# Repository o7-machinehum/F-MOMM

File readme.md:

# F-MOMM
Flat Micro Outline Memory Module. A RAM memory module for SBC's. See blog post [here](https://machinehum.medium.com/upcycling-laptop-memory-for-single-board-computers-15ed4cf8a675).

## Helping out
This project is in it's infancy. If you're interested in contributing join the [discord here](https://discord.com/invite/EtZT7mjNuM).

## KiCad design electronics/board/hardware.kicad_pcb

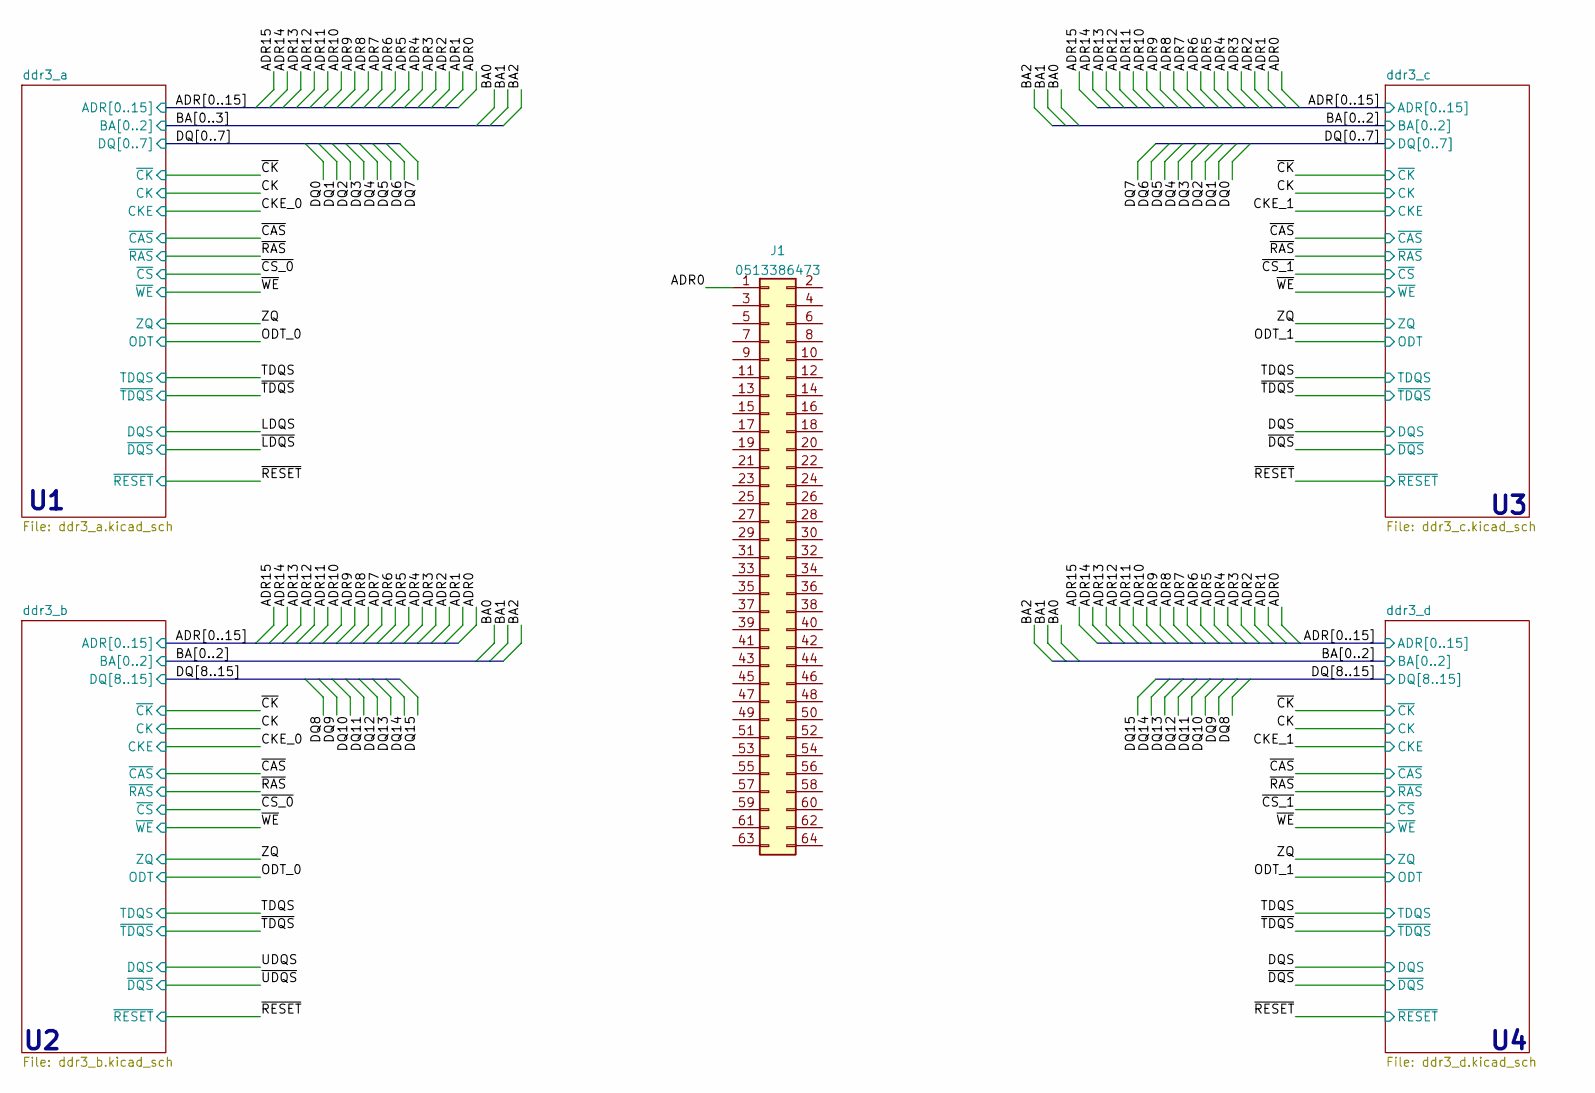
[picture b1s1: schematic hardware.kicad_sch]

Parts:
J1: 0513386473

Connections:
/ADR0: J1.1; also elsewhere on the board

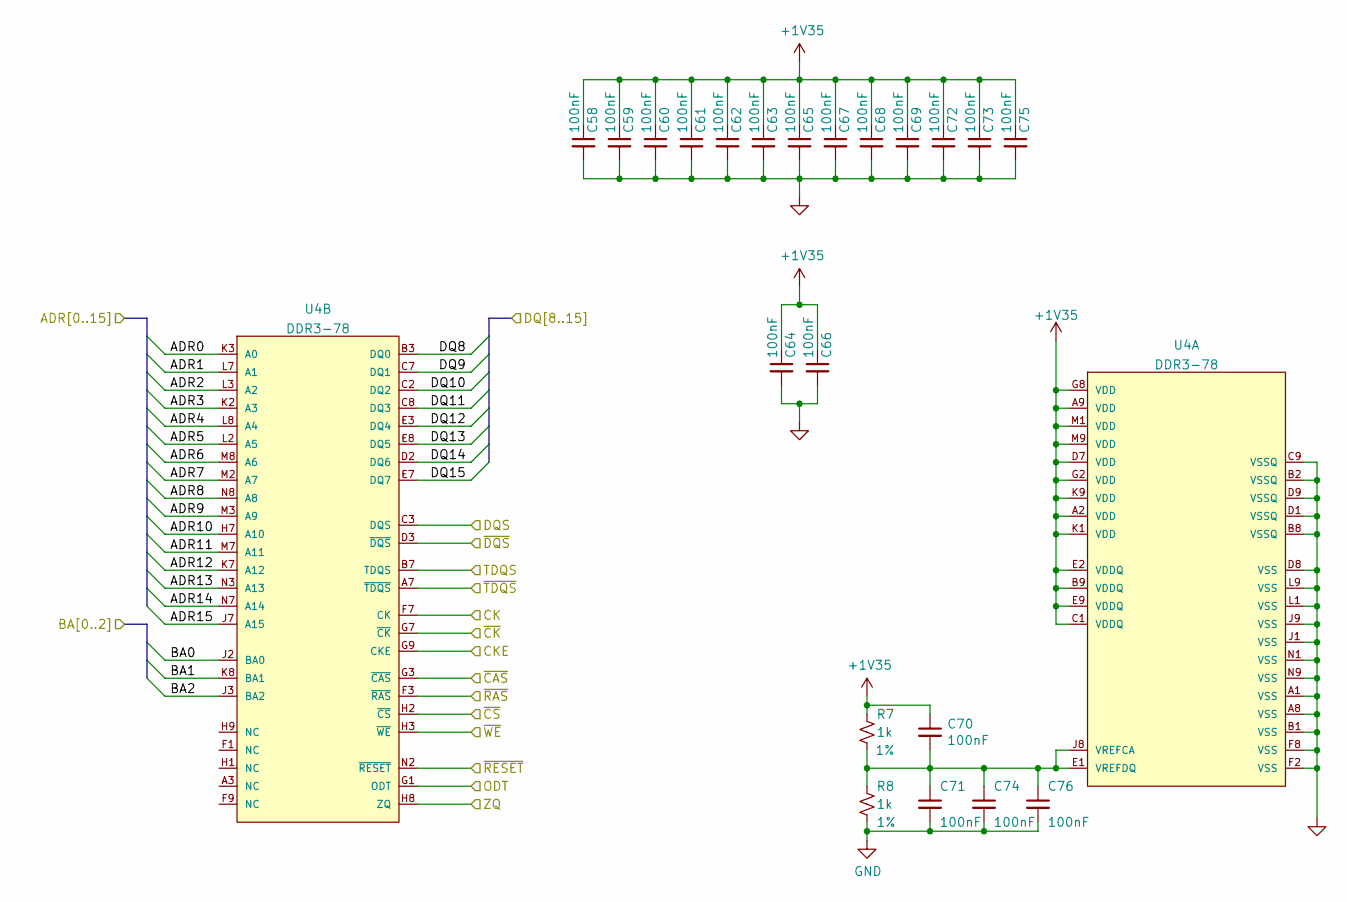
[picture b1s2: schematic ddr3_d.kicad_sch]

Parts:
C58, C59, C60, C61, C62, C63, C64, C65, C66, C67, C68, C69, C70, C71, C72, C73, C74, C75, C76: 100nF; C_0402_1005Metric; MPN CC0402KRX7R7BB104
R7, R8: 1k; R_0402_1005Metric; Tolerance 1%; MPN 4-1879208-9
U4: DDR3-78; DDR3-BGA-78-Tightest

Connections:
+1V35: C58.1, C59.1, C60.1, C61.1, C62.1, C63.1, C64.1, C65.1, C66.1, C67.1, C68.1, C69.1, C70.1, C72.1, C73.1, C75.1, R7.1, U4.A2 (VDD), U4.A9 (VDD), U4.B9 (VDDQ), U4.C1 (VDDQ), U4.D7 (VDD), U4.E2 (VDDQ), U4.E9 (VDDQ), U4.G2 (VDD), U4.G8 (VDD), U4.K1 (VDD), U4.K9 (VDD), U4.M1 (VDD), U4.M9 (VDD); also elsewhere on the board
/ADR0: U4.K3 (A0); also elsewhere on the board
/ADR1: U4.L7 (A1); also elsewhere on the board
/ADR2: U4.L3 (A2); also elsewhere on the board
/ADR3: U4.K2 (A3); also elsewhere on the board
/ADR4: U4.L8 (A4); also elsewhere on the board
/ADR5: U4.L2 (A5); also elsewhere on the board
/ADR6: U4.M8 (A6); also elsewhere on the board
/ADR7: U4.M2 (A7); also elsewhere on the board
/ADR8: U4.N8 (A8); also elsewhere on the board
/ADR9: U4.M3 (A9); also elsewhere on the board
/ADR10: U4.H7 (A10); also elsewhere on the board
/ADR11: U4.M7 (A11); also elsewhere on the board
/ADR12: U4.K7 (A12); also elsewhere on the board
/ADR13: U4.N3 (A13); also elsewhere on the board
/ADR14: U4.N7 (A14); also elsewhere on the board
/ADR15: U4.J7 (A15); also elsewhere on the board
/BA0: U4.J2 (BA0); also elsewhere on the board
/BA1: U4.K8 (BA1); also elsewhere on the board
/BA2: U4.J3 (BA2); also elsewhere on the board
/CK: U4.F7 (CK); also elsewhere on the board
/CKE_1: U4.G9 (CKE); also elsewhere on the board
/DQ8: U4.B3 (DQ0)
/DQ9: U4.C7 (DQ1)
/DQ10: U4.C2 (DQ2)
/DQ11: U4.C8 (DQ3)
/DQ12: U4.E3 (DQ4)
/DQ13: U4.E8 (DQ5)
/DQ14: U4.D2 (DQ6)
/DQ15: U4.E7 (DQ7)
/DQS: U4.C3 (DQS); also elsewhere on the board
/ODT_1: U4.G1 (ODT); also elsewhere on the board
/TDQS: U4.B7 (TDQS); also elsewhere on the board
/ZQ: U4.H8 (ZQ); also elsewhere on the board
/~CAS: U4.G3 (~CAS); also elsewhere on the board
/~CK: U4.G7 (~CK); also elsewhere on the board
/~CS_1: U4.H2 (~CS); also elsewhere on the board
/~DQS: U4.D3 (~DQS); also elsewhere on the board
/~RAS: U4.F3 (~RAS); also elsewhere on the board
/~RESET: U4.N2 (~RESET); also elsewhere on the board
/~TDQS: U4.A7 (~TDQS); also elsewhere on the board
/~WE: U4.H3 (~WE); also elsewhere on the board
GND: C58.2, C59.2, C60.2, C61.2, C62.2, C63.2, C64.2, C65.2, C66.2, C67.2, C68.2, C69.2, C71.2, C72.2, C73.2, C74.2, C75.2, C76.2, R8.2, U4.A1 (VSS), U4.A8 (VSS), U4.B1 (VSS), U4.B2 (VSSQ), U4.B8 (VSSQ), U4.C9 (VSSQ), U4.D1 (VSSQ), U4.D8 (VSS), U4.D9 (VSSQ), U4.F2 (VSS), U4.F8 (VSS), U4.J1 (VSS), U4.J9 (VSS), U4.L1 (VSS), U4.L9 (VSS), U4.N1 (VSS), U4.N9 (VSS); also elsewhere on the board
unnamed: C70.2, C71.1, C74.1, C76.1, R7.2, R8.1, U4.E1 (VREFDQ), U4.J8 (VREFCA)

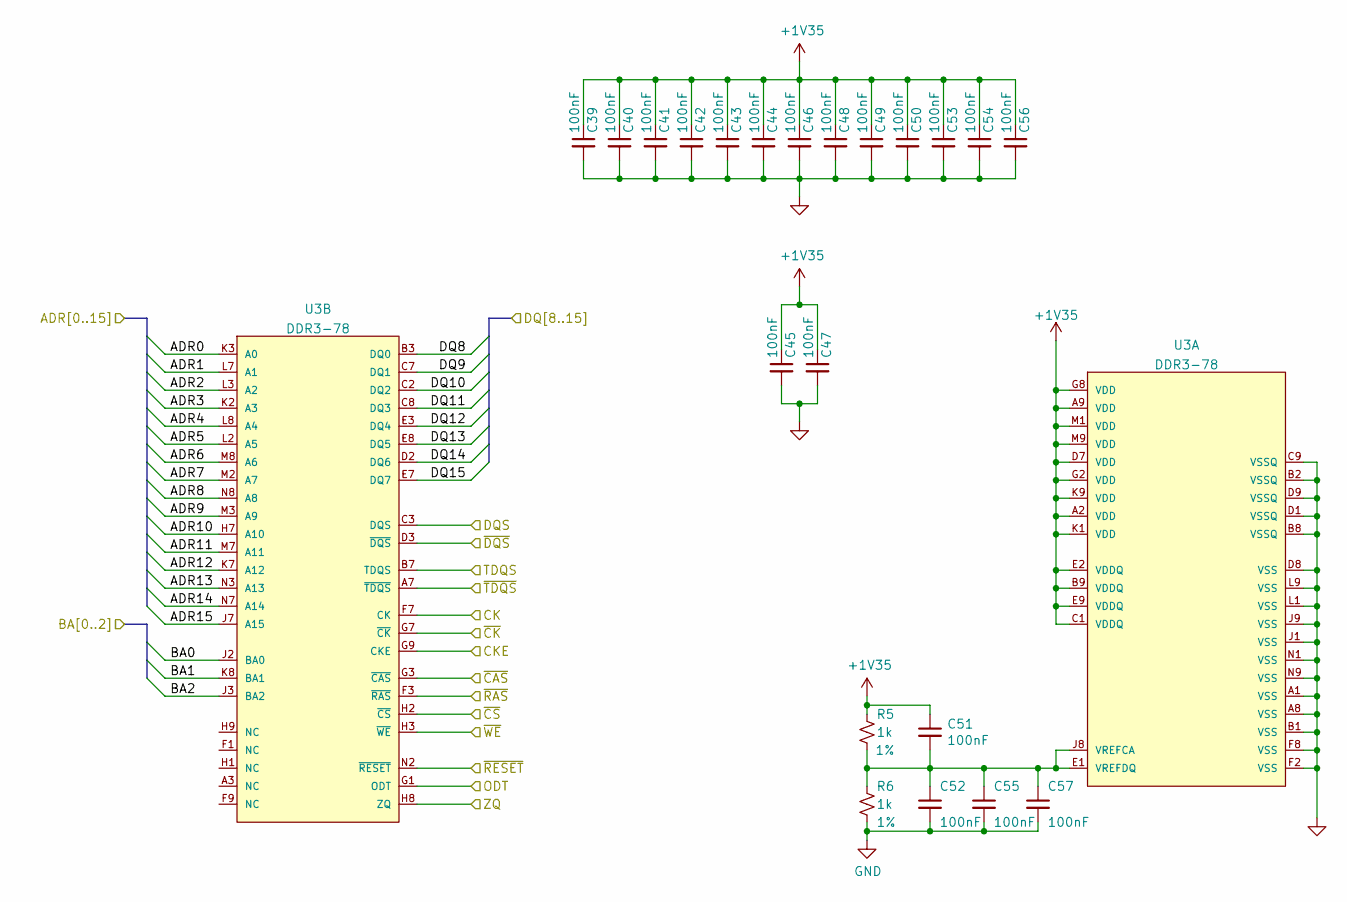
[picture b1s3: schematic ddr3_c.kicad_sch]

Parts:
C39, C40, C41, C42, C43, C44, C45, C46, C47, C48, C49, C50, C51, C52, C53, C54, C55, C56, C57: 100nF; C_0402_1005Metric; MPN CC0402KRX7R7BB104
R5, R6: 1k; R_0402_1005Metric; Tolerance 1%; MPN 4-1879208-9
U3: DDR3-78; DDR3-BGA-78-Tightest

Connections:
+1V35: C39.1, C40.1, C41.1, C42.1, C43.1, C44.1, C45.1, C46.1, C47.1, C48.1, C49.1, C50.1, C51.1, C53.1, C54.1, C56.1, R5.1, U3.A2 (VDD), U3.A9 (VDD), U3.B9 (VDDQ), U3.C1 (VDDQ), U3.D7 (VDD), U3.E2 (VDDQ), U3.E9 (VDDQ), U3.G2 (VDD), U3.G8 (VDD), U3.K1 (VDD), U3.K9 (VDD), U3.M1 (VDD), U3.M9 (VDD); also elsewhere on the board
/ADR0: U3.K3 (A0); also elsewhere on the board
/ADR1: U3.L7 (A1); also elsewhere on the board
/ADR2: U3.L3 (A2); also elsewhere on the board
/ADR3: U3.K2 (A3); also elsewhere on the board
/ADR4: U3.L8 (A4); also elsewhere on the board
/ADR5: U3.L2 (A5); also elsewhere on the board
/ADR6: U3.M8 (A6); also elsewhere on the board
/ADR7: U3.M2 (A7); also elsewhere on the board
/ADR8: U3.N8 (A8); also elsewhere on the board
/ADR9: U3.M3 (A9); also elsewhere on the board
/ADR10: U3.H7 (A10); also elsewhere on the board
/ADR11: U3.M7 (A11); also elsewhere on the board
/ADR12: U3.K7 (A12); also elsewhere on the board
/ADR13: U3.N3 (A13); also elsewhere on the board
/ADR14: U3.N7 (A14); also elsewhere on the board
/ADR15: U3.J7 (A15); also elsewhere on the board
/BA0: U3.J2 (BA0); also elsewhere on the board
/BA1: U3.K8 (BA1); also elsewhere on the board
/BA2: U3.J3 (BA2); also elsewhere on the board
/CK: U3.F7 (CK); also elsewhere on the board
/CKE_1: U3.G9 (CKE); also elsewhere on the board
/DQS: U3.C3 (DQS); also elsewhere on the board
/ODT_1: U3.G1 (ODT); also elsewhere on the board
/TDQS: U3.B7 (TDQS); also elsewhere on the board
/ZQ: U3.H8 (ZQ); also elsewhere on the board
/ddr3_c/DQ8: U3.B3 (DQ0)
/ddr3_c/DQ9: U3.C7 (DQ1)
/ddr3_c/DQ10: U3.C2 (DQ2)
/ddr3_c/DQ11: U3.C8 (DQ3)
/ddr3_c/DQ12: U3.E3 (DQ4)
/ddr3_c/DQ13: U3.E8 (DQ5)
/ddr3_c/DQ14: U3.D2 (DQ6)
/ddr3_c/DQ15: U3.E7 (DQ7)
/~CAS: U3.G3 (~CAS); also elsewhere on the board
/~CK: U3.G7 (~CK); also elsewhere on the board
/~CS_1: U3.H2 (~CS); also elsewhere on the board
/~DQS: U3.D3 (~DQS); also elsewhere on the board
/~RAS: U3.F3 (~RAS); also elsewhere on the board
/~RESET: U3.N2 (~RESET); also elsewhere on the board
/~TDQS: U3.A7 (~TDQS); also elsewhere on the board
/~WE: U3.H3 (~WE); also elsewhere on the board
GND: C39.2, C40.2, C41.2, C42.2, C43.2, C44.2, C45.2, C46.2, C47.2, C48.2, C49.2, C50.2, C52.2, C53.2, C54.2, C55.2, C56.2, C57.2, R6.2, U3.A1 (VSS), U3.A8 (VSS), U3.B1 (VSS), U3.B2 (VSSQ), U3.B8 (VSSQ), U3.C9 (VSSQ), U3.D1 (VSSQ), U3.D8 (VSS), U3.D9 (VSSQ), U3.F2 (VSS), U3.F8 (VSS), U3.J1 (VSS), U3.J9 (VSS), U3.L1 (VSS), U3.L9 (VSS), U3.N1 (VSS), U3.N9 (VSS); also elsewhere on the board
unnamed: C51.2, C52.1, C55.1, C57.1, R5.2, R6.1, U3.E1 (VREFDQ), U3.J8 (VREFCA)

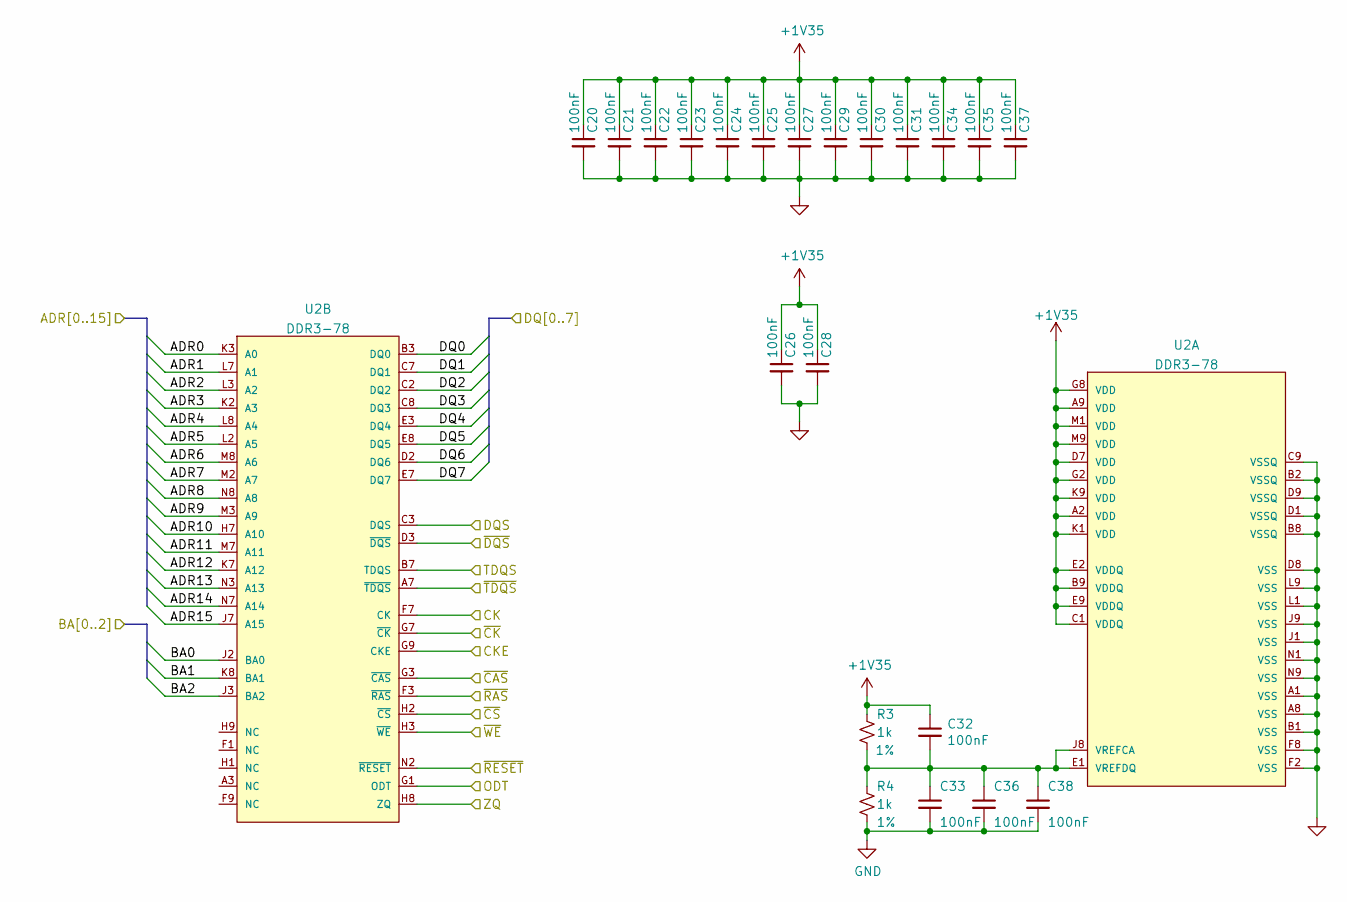
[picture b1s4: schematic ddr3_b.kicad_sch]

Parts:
C20, C21, C22, C23, C24, C25, C26, C27, C28, C29, C30, C31, C32, C33, C34, C35, C36, C37, C38: 100nF; C_0402_1005Metric; MPN CC0402KRX7R7BB104
R3, R4: 1k; R_0402_1005Metric; Tolerance 1%; MPN 4-1879208-9
U2: DDR3-78; DDR3-BGA-78-Tightest

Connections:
+1V35: C20.1, C21.1, C22.1, C23.1, C24.1, C25.1, C26.1, C27.1, C28.1, C29.1, C30.1, C31.1, C32.1, C34.1, C35.1, C37.1, R3.1, U2.A2 (VDD), U2.A9 (VDD), U2.B9 (VDDQ), U2.C1 (VDDQ), U2.D7 (VDD), U2.E2 (VDDQ), U2.E9 (VDDQ), U2.G2 (VDD), U2.G8 (VDD), U2.K1 (VDD), U2.K9 (VDD), U2.M1 (VDD), U2.M9 (VDD); also elsewhere on the board
/ADR0: U2.K3 (A0); also elsewhere on the board
/ADR1: U2.L7 (A1); also elsewhere on the board
/ADR2: U2.L3 (A2); also elsewhere on the board
/ADR3: U2.K2 (A3); also elsewhere on the board
/ADR4: U2.L8 (A4); also elsewhere on the board
/ADR5: U2.L2 (A5); also elsewhere on the board
/ADR6: U2.M8 (A6); also elsewhere on the board
/ADR7: U2.M2 (A7); also elsewhere on the board
/ADR8: U2.N8 (A8); also elsewhere on the board
/ADR9: U2.M3 (A9); also elsewhere on the board
/ADR10: U2.H7 (A10); also elsewhere on the board
/ADR11: U2.M7 (A11); also elsewhere on the board
/ADR12: U2.K7 (A12); also elsewhere on the board
/ADR13: U2.N3 (A13); also elsewhere on the board
/ADR14: U2.N7 (A14); also elsewhere on the board
/ADR15: U2.J7 (A15); also elsewhere on the board
/BA0: U2.J2 (BA0); also elsewhere on the board
/BA1: U2.K8 (BA1); also elsewhere on the board
/BA2: U2.J3 (BA2); also elsewhere on the board
/CK: U2.F7 (CK); also elsewhere on the board
/CKE_0: U2.G9 (CKE); also elsewhere on the board
/ODT_0: U2.G1 (ODT); also elsewhere on the board
/TDQS: U2.B7 (TDQS); also elsewhere on the board
/UDQS: U2.C3 (DQS)
/ZQ: U2.H8 (ZQ); also elsewhere on the board
/ddr3_b/DQ0: U2.B3 (DQ0)
/ddr3_b/DQ1: U2.C7 (DQ1)
/ddr3_b/DQ2: U2.C2 (DQ2)
/ddr3_b/DQ3: U2.C8 (DQ3)
/ddr3_b/DQ4: U2.E3 (DQ4)
/ddr3_b/DQ5: U2.E8 (DQ5)
/ddr3_b/DQ6: U2.D2 (DQ6)
/ddr3_b/DQ7: U2.E7 (DQ7)
/~CAS: U2.G3 (~CAS); also elsewhere on the board
/~CK: U2.G7 (~CK); also elsewhere on the board
/~CS_0: U2.H2 (~CS); also elsewhere on the board
/~RAS: U2.F3 (~RAS); also elsewhere on the board
/~RESET: U2.N2 (~RESET); also elsewhere on the board
/~TDQS: U2.A7 (~TDQS); also elsewhere on the board
/~UDQS: U2.D3 (~DQS)
/~WE: U2.H3 (~WE); also elsewhere on the board
GND: C20.2, C21.2, C22.2, C23.2, C24.2, C25.2, C26.2, C27.2, C28.2, C29.2, C30.2, C31.2, C33.2, C34.2, C35.2, C36.2, C37.2, C38.2, R4.2, U2.A1 (VSS), U2.A8 (VSS), U2.B1 (VSS), U2.B2 (VSSQ), U2.B8 (VSSQ), U2.C9 (VSSQ), U2.D1 (VSSQ), U2.D8 (VSS), U2.D9 (VSSQ), U2.F2 (VSS), U2.F8 (VSS), U2.J1 (VSS), U2.J9 (VSS), U2.L1 (VSS), U2.L9 (VSS), U2.N1 (VSS), U2.N9 (VSS); also elsewhere on the board
unnamed: C32.2, C33.1, C36.1, C38.1, R3.2, R4.1, U2.E1 (VREFDQ), U2.J8 (VREFCA)

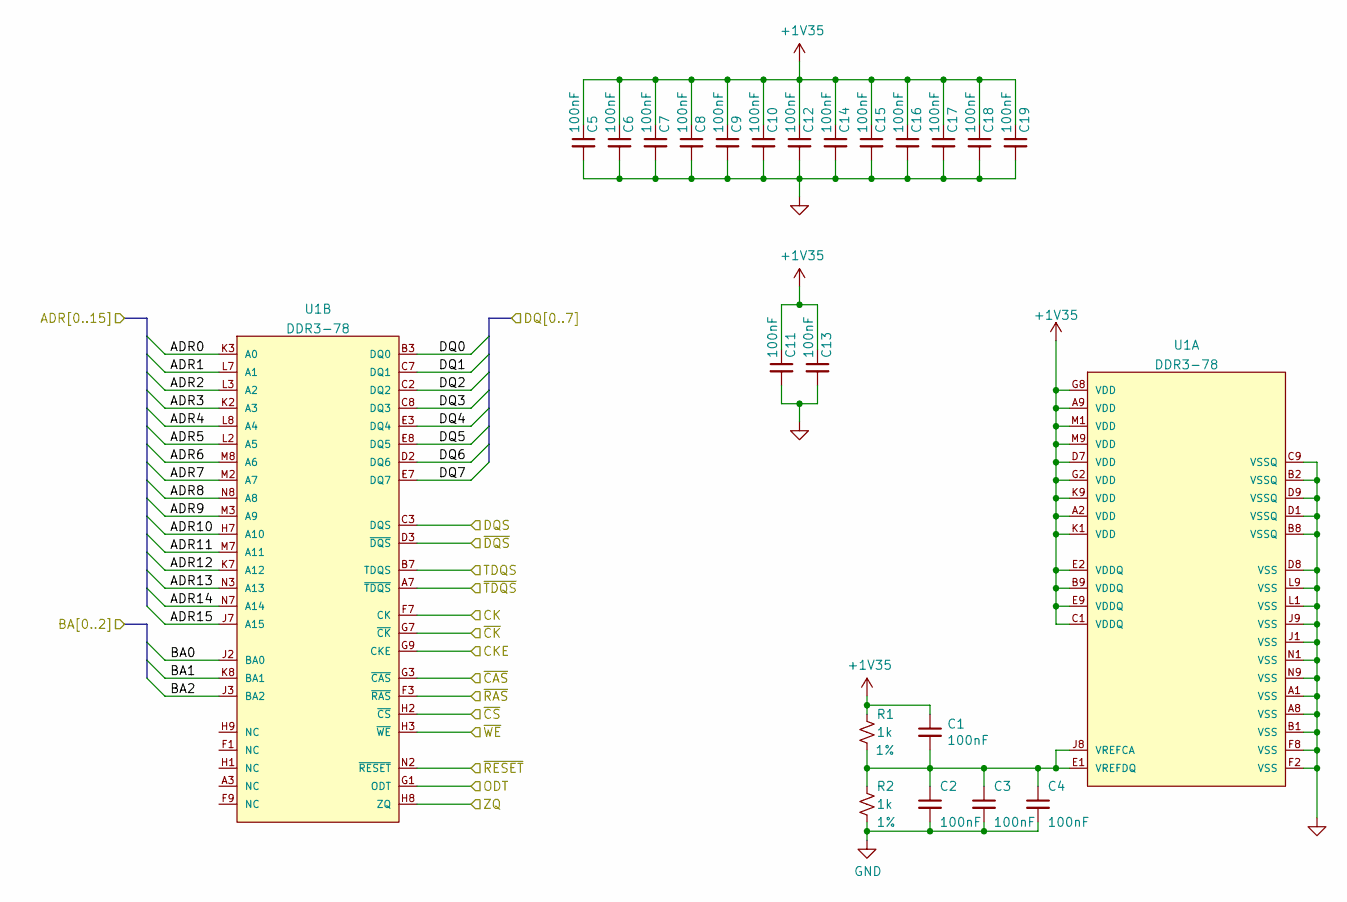
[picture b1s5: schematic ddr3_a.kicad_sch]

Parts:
C1, C2, C3, C4, C5, C6, C7, C8, C9, C10, C11, C12, C13, C14, C15, C16, C17, C18, C19: 100nF; C_0402_1005Metric; MPN CC0402KRX7R7BB104
R1, R2: 1k; R_0402_1005Metric; Tolerance 1%; MPN 4-1879208-9
U1: DDR3-78; DDR3-BGA-78-Tightest

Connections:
+1V35: C1.1, C5.1, C6.1, C7.1, C8.1, C9.1, C10.1, C11.1, C12.1, C13.1, C14.1, C15.1, C16.1, C17.1, C18.1, C19.1, R1.1, U1.A2 (VDD), U1.A9 (VDD), U1.B9 (VDDQ), U1.C1 (VDDQ), U1.D7 (VDD), U1.E2 (VDDQ), U1.E9 (VDDQ), U1.G2 (VDD), U1.G8 (VDD), U1.K1 (VDD), U1.K9 (VDD), U1.M1 (VDD), U1.M9 (VDD); also elsewhere on the board
/ADR0: U1.K3 (A0); also elsewhere on the board
/ADR1: U1.L7 (A1); also elsewhere on the board
/ADR2: U1.L3 (A2); also elsewhere on the board
/ADR3: U1.K2 (A3); also elsewhere on the board
/ADR4: U1.L8 (A4); also elsewhere on the board
/ADR5: U1.L2 (A5); also elsewhere on the board
/ADR6: U1.M8 (A6); also elsewhere on the board
/ADR7: U1.M2 (A7); also elsewhere on the board
/ADR8: U1.N8 (A8); also elsewhere on the board
/ADR9: U1.M3 (A9); also elsewhere on the board
/ADR10: U1.H7 (A10); also elsewhere on the board
/ADR11: U1.M7 (A11); also elsewhere on the board
/ADR12: U1.K7 (A12); also elsewhere on the board
/ADR13: U1.N3 (A13); also elsewhere on the board
/ADR14: U1.N7 (A14); also elsewhere on the board
/ADR15: U1.J7 (A15); also elsewhere on the board
/BA0: U1.J2 (BA0); also elsewhere on the board
/BA1: U1.K8 (BA1); also elsewhere on the board
/BA2: U1.J3 (BA2); also elsewhere on the board
/CK: U1.F7 (CK); also elsewhere on the board
/CKE_0: U1.G9 (CKE); also elsewhere on the board
/DQ0: U1.B3 (DQ0)
/DQ1: U1.C7 (DQ1)
/DQ2: U1.C2 (DQ2)
/DQ3: U1.C8 (DQ3)
/DQ4: U1.E3 (DQ4)
/DQ5: U1.E8 (DQ5)
/DQ6: U1.D2 (DQ6)
/DQ7: U1.E7 (DQ7)
/LDQS: U1.C3 (DQS)
/ODT_0: U1.G1 (ODT); also elsewhere on the board
/TDQS: U1.B7 (TDQS); also elsewhere on the board
/ZQ: U1.H8 (ZQ); also elsewhere on the board
/~CAS: U1.G3 (~CAS); also elsewhere on the board
/~CK: U1.G7 (~CK); also elsewhere on the board
/~CS_0: U1.H2 (~CS); also elsewhere on the board
/~LDQS: U1.D3 (~DQS)
/~RAS: U1.F3 (~RAS); also elsewhere on the board
/~RESET: U1.N2 (~RESET); also elsewhere on the board
/~TDQS: U1.A7 (~TDQS); also elsewhere on the board
/~WE: U1.H3 (~WE); also elsewhere on the board
GND: C2.2, C3.2, C4.2, C5.2, C6.2, C7.2, C8.2, C9.2, C10.2, C11.2, C12.2, C13.2, C14.2, C15.2, C16.2, C17.2, C18.2, C19.2, R2.2, U1.A1 (VSS), U1.A8 (VSS), U1.B1 (VSS), U1.B2 (VSSQ), U1.B8 (VSSQ), U1.C9 (VSSQ), U1.D1 (VSSQ), U1.D8 (VSS), U1.D9 (VSSQ), U1.F2 (VSS), U1.F8 (VSS), U1.J1 (VSS), U1.J9 (VSS), U1.L1 (VSS), U1.L9 (VSS), U1.N1 (VSS), U1.N9 (VSS); also elsewhere on the board
unnamed: C1.2, C2.1, C3.1, C4.1, R1.2, R2.1, U1.E1 (VREFDQ), U1.J8 (VREFCA)

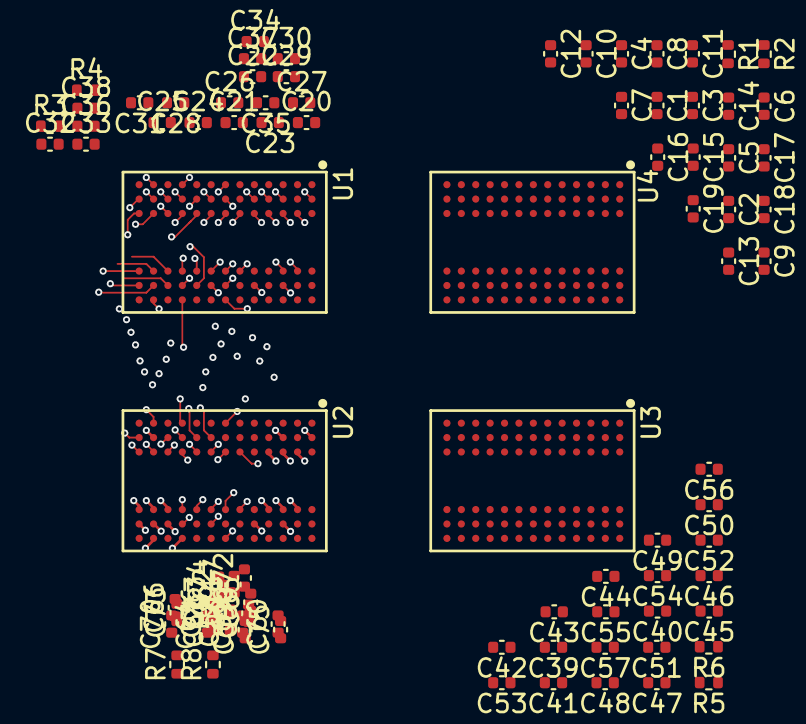
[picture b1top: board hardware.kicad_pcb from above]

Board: 6 copper layers, 89 parts (1 on the bottom side), 42 nets.

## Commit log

2022-01-23 Initial commit.
2022-01-23 Added the board files.
2022-02-08 Added the schematics for the rams and stuff.
2022-02-09 Added gitignore, fixed the part
2022-02-11 Working on the routing.
